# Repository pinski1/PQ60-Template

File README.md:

#PQ60-Template
A template board and schematic in Eagle 7.2 for the Pocket Qube 60 standard.

**Untested**

A very simple template in Eagle 7.2 which has the connectors in the right places, with the right net names and the right connections made.

Please note that the locating pegs for the top and bottom PQ60 connectors are 0.3mm out, this is due to different offsets in the Hirose datasheet, 1.5mm and 1.8mm respectively.

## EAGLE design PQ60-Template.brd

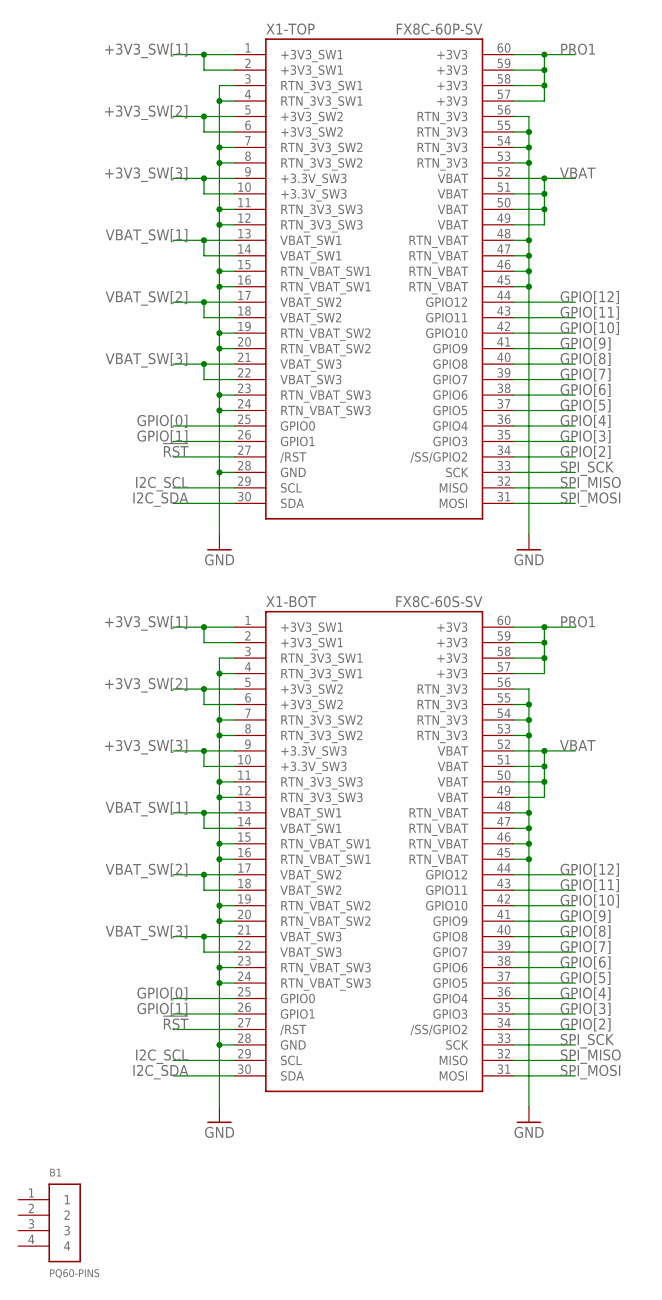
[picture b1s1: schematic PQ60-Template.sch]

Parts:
B1: PQ60-PINS; PQ60_PINS
X1-BOT: FX8C-60S-SV
X1-TOP: FX8C-60P-SV

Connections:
!RST: X1-BOT.27 (/RST), X1-TOP.27 (/RST)
+3V3_SW[1]: X1-BOT.1 (+3V3_SW1), X1-BOT.2 (+3V3_SW1), X1-TOP.1 (+3V3_SW1), X1-TOP.2 (+3V3_SW1)
+3V3_SW[2]: X1-BOT.5 (+3V3_SW2), X1-BOT.6 (+3V3_SW2), X1-TOP.5 (+3V3_SW2), X1-TOP.6 (+3V3_SW2)
+3V3_SW[3]: X1-BOT.9 (+3.3V_SW3), X1-BOT.10 (+3.3V_SW3), X1-TOP.9 (+3.3V_SW3), X1-TOP.10 (+3.3V_SW3)
GND: X1-BOT.3 (RTN_3V3_SW1), X1-BOT.4 (RTN_3V3_SW1), X1-BOT.7 (RTN_3V3_SW2), X1-BOT.8 (RTN_3V3_SW2), X1-BOT.11 (RTN_3V3_SW3), X1-BOT.12 (RTN_3V3_SW3), X1-BOT.15 (RTN_VBAT_SW1), X1-BOT.16 (RTN_VBAT_SW1), X1-BOT.19 (RTN_VBAT_SW2), X1-BOT.20 (RTN_VBAT_SW2), X1-BOT.23 (RTN_VBAT_SW3), X1-BOT.24 (RTN_VBAT_SW3), X1-BOT.28 (GND), X1-BOT.45 (RTN_VBAT), X1-BOT.46 (RTN_VBAT), X1-BOT.47 (RTN_VBAT), X1-BOT.48 (RTN_VBAT), X1-BOT.53 (RTN_3V3), X1-BOT.54 (RTN_3V3), X1-BOT.55 (RTN_3V3), X1-BOT.56 (RTN_3V3), X1-TOP.3 (RTN_3V3_SW1), X1-TOP.4 (RTN_3V3_SW1), X1-TOP.7 (RTN_3V3_SW2), X1-TOP.8 (RTN_3V3_SW2), X1-TOP.11 (RTN_3V3_SW3), X1-TOP.12 (RTN_3V3_SW3), X1-TOP.15 (RTN_VBAT_SW1), X1-TOP.16 (RTN_VBAT_SW1), X1-TOP.19 (RTN_VBAT_SW2), X1-TOP.20 (RTN_VBAT_SW2), X1-TOP.23 (RTN_VBAT_SW3), X1-TOP.24 (RTN_VBAT_SW3), X1-TOP.28 (GND), X1-TOP.45 (RTN_VBAT), X1-TOP.46 (RTN_VBAT), X1-TOP.47 (RTN_VBAT), X1-TOP.48 (RTN_VBAT), X1-TOP.53 (RTN_3V3), X1-TOP.54 (RTN_3V3), X1-TOP.55 (RTN_3V3), X1-TOP.56 (RTN_3V3)
GPIO[0]: X1-BOT.25 (GPIO0), X1-TOP.25 (GPIO0)
GPIO[1]: X1-BOT.26 (GPIO1), X1-TOP.26 (GPIO1)
GPIO[2]: X1-BOT.34 (/SS/GPIO2), X1-TOP.34 (/SS/GPIO2)
GPIO[3]: X1-BOT.35 (GPIO3), X1-TOP.35 (GPIO3)
GPIO[4]: X1-BOT.36 (GPIO4), X1-TOP.36 (GPIO4)
GPIO[5]: X1-BOT.37 (GPIO5), X1-TOP.37 (GPIO5)
GPIO[6]: X1-BOT.38 (GPIO6), X1-TOP.38 (GPIO6)
GPIO[7]: X1-BOT.39 (GPIO7), X1-TOP.39 (GPIO7)
GPIO[8]: X1-BOT.40 (GPIO8), X1-TOP.40 (GPIO8)
GPIO[9]: X1-BOT.41 (GPIO9), X1-TOP.41 (GPIO9)
GPIO[10]: X1-BOT.42 (GPIO10), X1-TOP.42 (GPIO10)
GPIO[11]: X1-BOT.43 (GPIO11), X1-TOP.43 (GPIO11)
GPIO[12]: X1-BOT.44 (GPIO12), X1-TOP.44 (GPIO12)
I2C_SCL: X1-BOT.29 (SCL), X1-TOP.29 (SCL)
I2C_SDA: X1-BOT.30 (SDA), X1-TOP.30 (SDA)
PRO1: X1-BOT.57 (+3V3), X1-BOT.58 (+3V3), X1-BOT.59 (+3V3), X1-BOT.60 (+3V3), X1-TOP.57 (+3V3), X1-TOP.58 (+3V3), X1-TOP.59 (+3V3), X1-TOP.60 (+3V3)
SPI_MISO: X1-BOT.32 (MISO), X1-TOP.32 (MISO)
SPI_MOSI: X1-BOT.31 (MOSI), X1-TOP.31 (MOSI)
SPI_SCK: X1-BOT.33 (SCK), X1-TOP.33 (SCK)
VBAT: X1-BOT.49 (VBAT), X1-BOT.50 (VBAT), X1-BOT.51 (VBAT), X1-BOT.52 (VBAT), X1-TOP.49 (VBAT), X1-TOP.50 (VBAT), X1-TOP.51 (VBAT), X1-TOP.52 (VBAT)
VBAT_SW[1]: X1-BOT.13 (VBAT_SW1), X1-BOT.14 (VBAT_SW1), X1-TOP.13 (VBAT_SW1), X1-TOP.14 (VBAT_SW1)
VBAT_SW[2]: X1-BOT.17 (VBAT_SW2), X1-BOT.18 (VBAT_SW2), X1-TOP.17 (VBAT_SW2), X1-TOP.18 (VBAT_SW2)
VBAT_SW[3]: X1-BOT.21 (VBAT_SW3), X1-BOT.22 (VBAT_SW3), X1-TOP.21 (VBAT_SW3), X1-TOP.22 (VBAT_SW3)

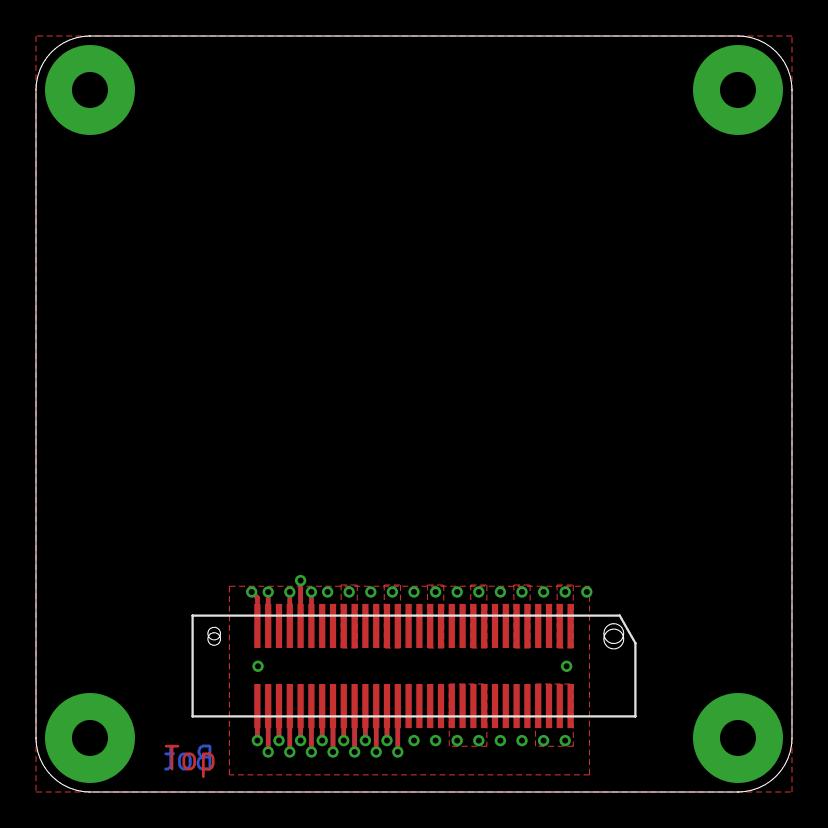
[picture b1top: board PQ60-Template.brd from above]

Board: 2 copper layers, 42.0 x 42.0 mm, 3 parts (1 on the bottom side), 28 nets.

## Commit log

2015-07-07 Update to new PQ60 v1.1 standard.
